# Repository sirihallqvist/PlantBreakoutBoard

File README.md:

# PlantBreakoutBoard

## Prerequisites:
- VSCode
- Arduino Nano 33 BLE connected via usb-usbc to the computer

- ADD MORE AS YOU GO HERE

## Install ArduinoCLI
1. Go to [Arduino CLI Download Page](https://arduino.github.io/arduino-cli/1.3/installation/)
2. Download the correct zip-folder
3. Place the folder where you want to have it
4. Add the path to the .exe file in PATH in environmental variables to be able to use it

## Set up Board

Run the following commands to update and download dependencies.

```powershell
arduino-cli core update-index
arduino-cli core install arduino:mbed_nano  # Installs needed board support for Arduino Nano 33 BLE
```

## Find the FQBN (Fully Qualified Board Name)

Run the following command to find the full name of the board:

```powershell
arduino-cli board listall
```

## Find the Port that the Arduino Use

Run the following command to find which port the Arduino board is using:

```powershell
arduino-cli board list
```

## Compile the Code

To compile the code, run the following command:

```powershell
arduino-cli compile --fqbn arduino:mbed_nano:nano33ble myProjectFolder  # if outside of the folder
arduino-cli compile --fqbn arduino:mbed_nano:nano33ble .  # if inside of the folder
```

## Upload the Code to the Arduino

To upload the code to the unit, run the following command:

```powershell
arduino-cli upload -p <PORT> --fqbn <FQBN> pathToYourProjectFile.ino
```

## Automatic Build and Upload in VSCode

Create the file .vscode/tasks.json in your repository, and add following content in that file:

```json
{
  "version": "2.0.0",
  "tasks": [
    {
      "label": "Build Arduino Sketch",
      "type": "powershell",
      "command": "arduino-cli compile --fqbn arduino:mbed_nano:nano33ble .",
      "group": "build"
    },
    {
      "label": "Upload Arduino Sketch",
      "type": "powershell",
      "command": "arduino-cli upload -p PORT --fqbn FQBN .",
      "group": "build"
    }
  ]
}
```

Now, to build and/or upload, press `Ctrl+Shift+B` and choose the task you want to do.

## Install BLE Library

To install the needed BLE Library, run the following command:

```powershell
arduino-cli lib install ArduinoBLE
```

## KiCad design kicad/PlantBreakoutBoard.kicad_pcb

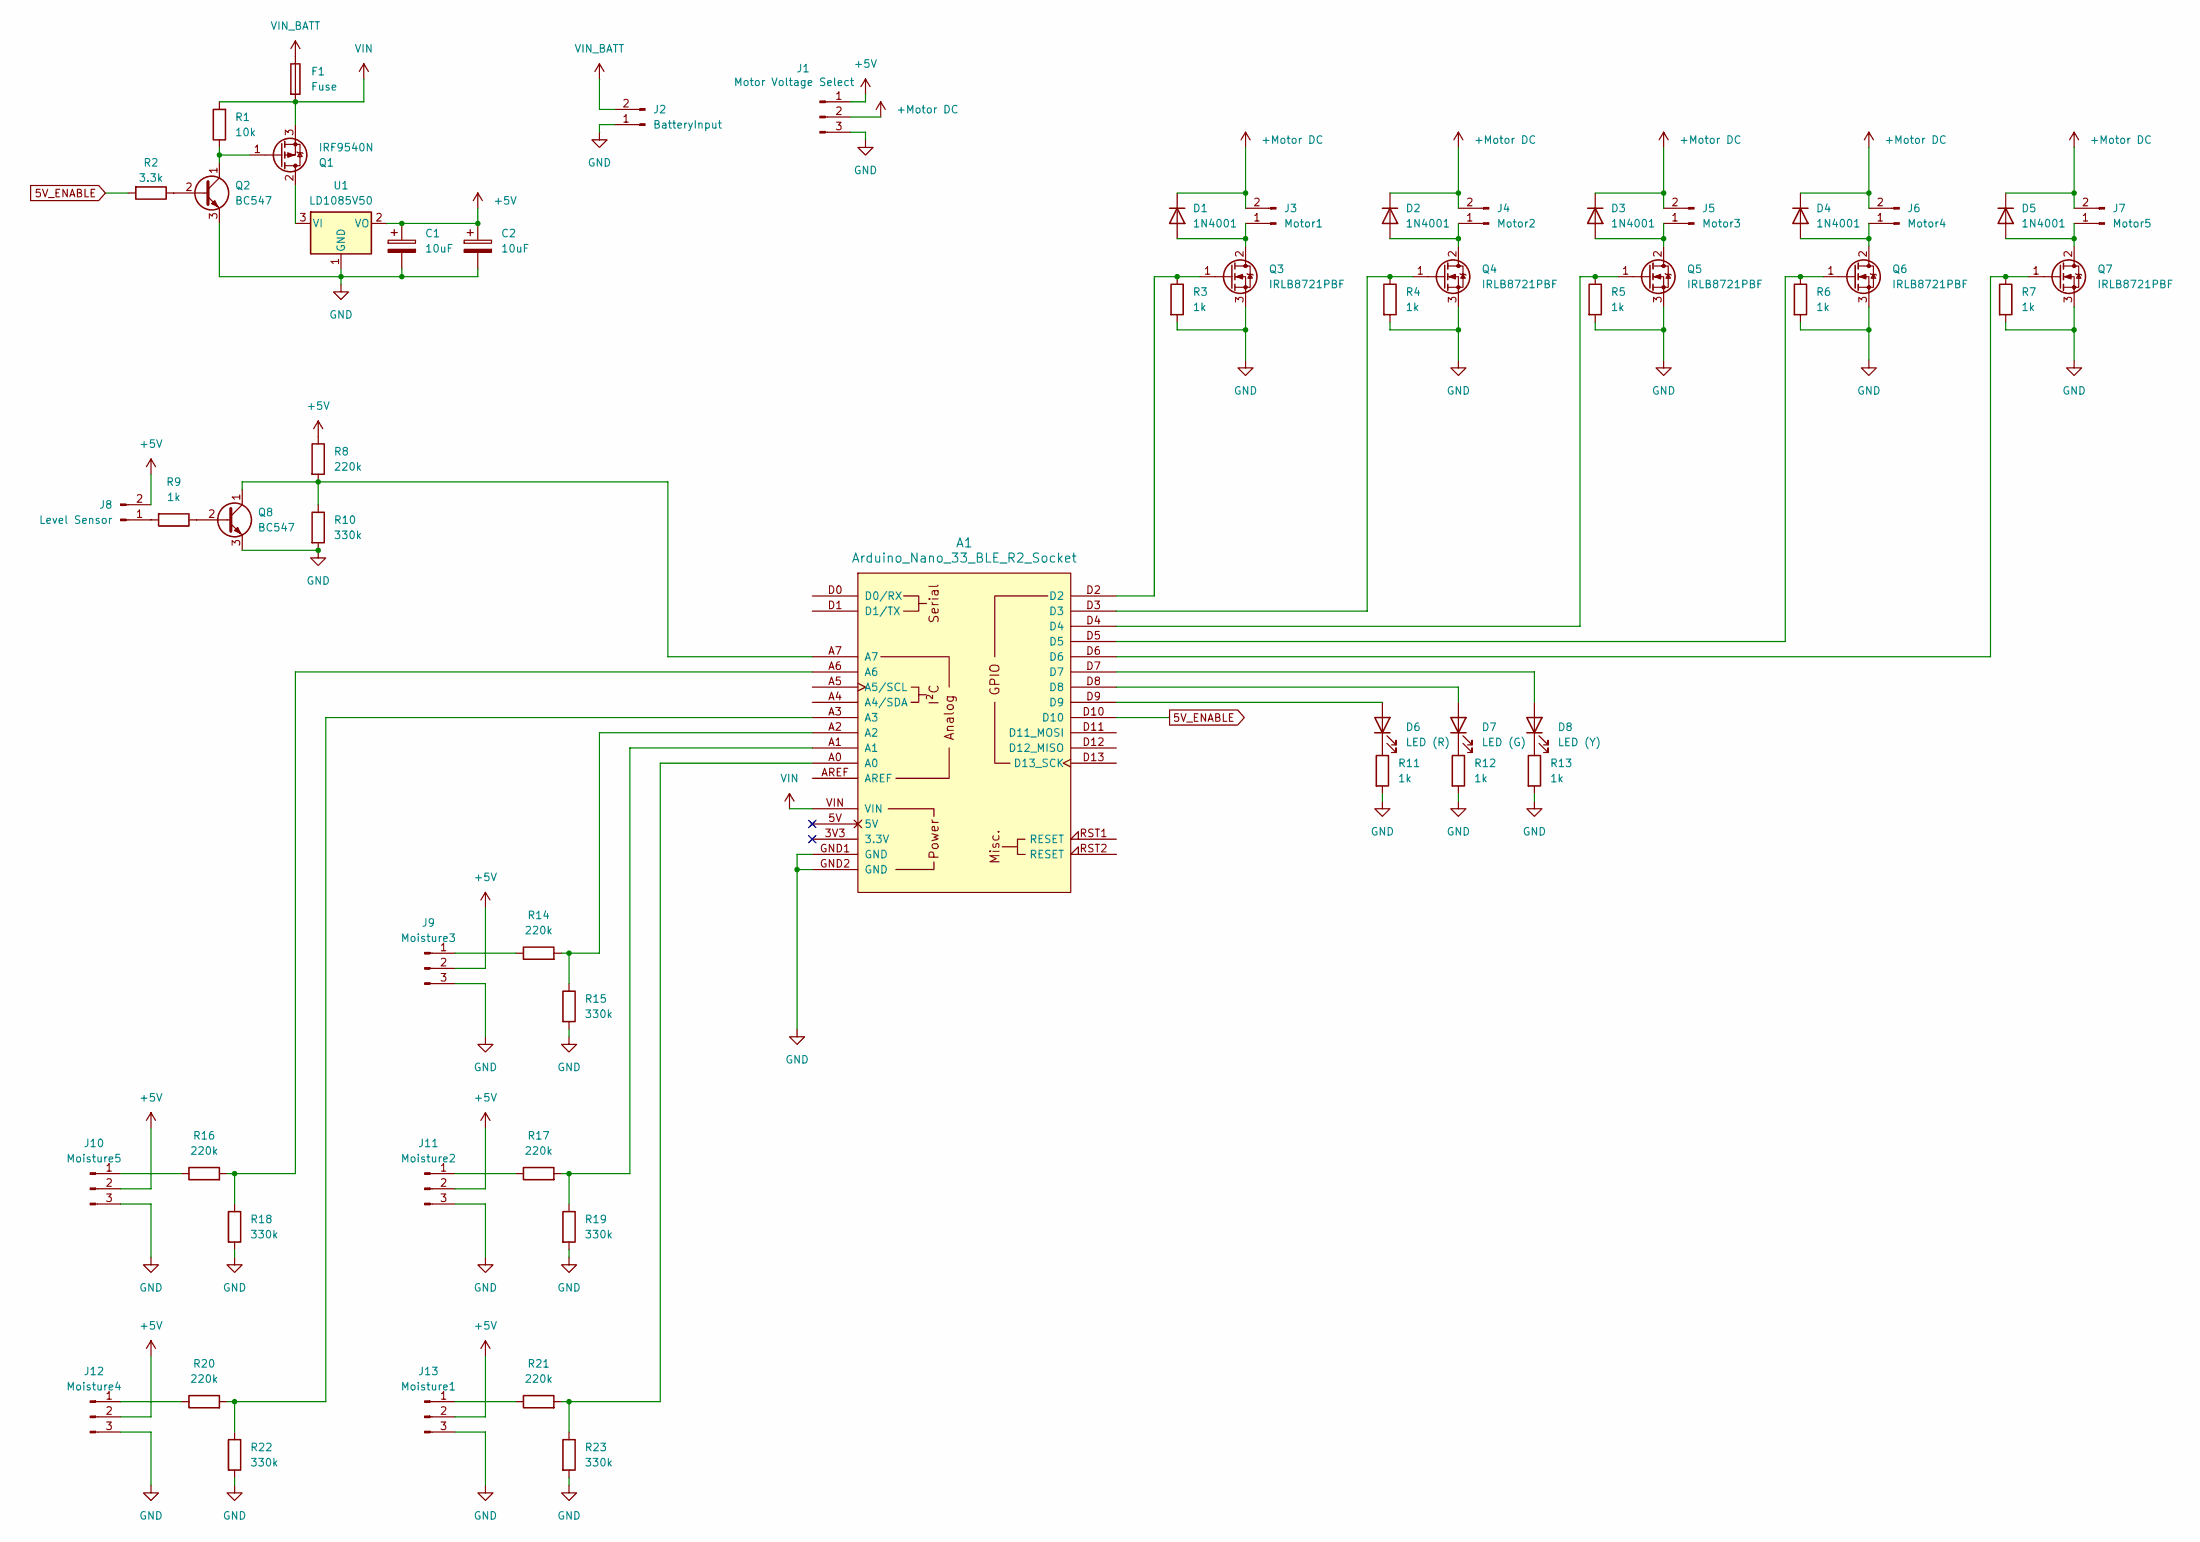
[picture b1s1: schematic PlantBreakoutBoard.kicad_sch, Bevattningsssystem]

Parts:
A1: Arduino_Nano_33_BLE_R2_Socket; Arduino_Nano_Every_Socket
C1, C2: 10uF; CP_Radial_D5.0mm_P2.00mm
D1, D2, D3, D4, D5: 1N4001; D_DO-41_SOD81_P10.16mm_Horizontal
D6: LED (R); LED_D3.0mm
D7: LED (G); LED_D3.0mm
D8: LED (Y); LED_D3.0mm
F1: Fuse; Fuseholder_Cylinder-5x20mm_Stelvio-Kontek_PTF78_Horizontal_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
J1: Motor Voltage Select; PinHeader_1x03_P2.54mm_Vertical
J2: BatteryInput; PinHeader_1x02_P2.54mm_Vertical
J3: Motor1; PinHeader_1x02_P2.54mm_Vertical
J4: Motor2; PinHeader_1x02_P2.54mm_Vertical
J5: Motor3; PinHeader_1x02_P2.54mm_Vertical
J6: Motor4; PinHeader_1x02_P2.54mm_Vertical
J7: Motor5; PinHeader_1x02_P2.54mm_Vertical
J8: Level Sensor; PinHeader_1x02_P2.54mm_Vertical
J9: Moisture3; PinHeader_1x03_P2.54mm_Vertical
J10: Moisture5; PinHeader_1x03_P2.54mm_Vertical
J11: Moisture2; PinHeader_1x03_P2.54mm_Vertical
J12: Moisture4; PinHeader_1x03_P2.54mm_Vertical
J13: Moisture1; PinHeader_1x03_P2.54mm_Vertical
Q1: IRF9540N; TO-220-3_Vertical
Q2, Q8: BC547; TO-92_Inline
Q3, Q4, Q5, Q6, Q7: IRLB8721PBF; TO-220-3_Vertical
R1: 10k; R_Axial_DIN0309_L9.0mm_D3.2mm_P12.70mm_Horizontal
R2: 3.3k; R_Axial_DIN0309_L9.0mm_D3.2mm_P12.70mm_Horizontal
R3, R4, R5, R6, R7, R9, R11, R12, R13: 1k; R_Axial_DIN0309_L9.0mm_D3.2mm_P12.70mm_Horizontal
R8, R14, R16, R17, R20, R21: 220k; R_Axial_DIN0309_L9.0mm_D3.2mm_P12.70mm_Horizontal
R10, R15, R18, R19, R22, R23: 330k; R_Axial_DIN0309_L9.0mm_D3.2mm_P12.70mm_Horizontal
U1: LD1085V50; TO-220-3_Vertical

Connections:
5V_ENABLE: A1.D10, R2.2
+5V: C1.1, C2.1, J1.1, J8.2, J9.2, J10.2, J11.2, J12.2, J13.2, R8.1, U1.2 (VO)
+Motor DC: D1.1 (K), D2.1 (K), D3.1 (K), D4.1 (K), D5.1 (K), J1.2, J3.2, J4.2, J5.2, J6.2, J7.2
GND: A1.GND1 (GND), A1.GND2 (GND), C1.2, C2.2, J1.3, J2.1, J9.3, J10.3, J11.3, J12.3, J13.3, Q2.3 (E), Q3.3 (S), Q4.3 (S), Q5.3 (S), Q6.3 (S), Q7.3 (S), Q8.3 (E), R3.2, R4.2, R5.2, R6.2, R7.2, R10.2, R11.2, R12.2, R13.2, R15.2, R18.2, R19.2, R22.2, R23.2, U1.1 (GND)
unnamed: A1.A0, R21.2, R23.1
unnamed: A1.A1, R17.2, R19.1
unnamed: A1.A2, R14.2, R15.1
unnamed: A1.A3, R20.2, R22.1
unnamed: A1.A6, R16.2, R18.1
unnamed: D1.2 (A), J3.1, Q3.2 (D)
unnamed: D2.2 (A), J4.1, Q4.2 (D)
unnamed: D3.2 (A), J5.1, Q5.2 (D)
unnamed: D4.2 (A), J6.1, Q6.2 (D)
unnamed: D5.2 (A), J7.1, Q7.2 (D)
unnamed: A1.D9, D6.2 (A)
unnamed: D6.1 (K), R11.1
unnamed: A1.D8, D7.2 (A)
unnamed: D7.1 (K), R12.1
unnamed: A1.D7, D8.2 (A)
unnamed: D8.1 (K), R13.1
unnamed: J8.1, R9.2
unnamed: J9.1, R14.1
unnamed: J10.1, R16.1
unnamed: J11.1, R17.1
unnamed: J12.1, R20.1
unnamed: J13.1, R21.1
unnamed: Q1.2 (D), U1.3 (VI)
unnamed: Q1.1 (G), Q2.1 (C), R1.1
unnamed: Q2.2 (B), R2.1
unnamed: A1.D2, Q3.1 (G), R3.1
unnamed: A1.D3, Q4.1 (G), R4.1
unnamed: A1.D4, Q5.1 (G), R5.1
unnamed: A1.D5, Q6.1 (G), R6.1
unnamed: A1.D6, Q7.1 (G), R7.1
unnamed: Q8.2 (B), R9.1
unnamed: A1.A7, Q8.1 (C), R8.2, R10.1
VIN: A1.VIN, F1.2, Q1.3 (S), R1.2
VIN_BATT: F1.1, J2.2

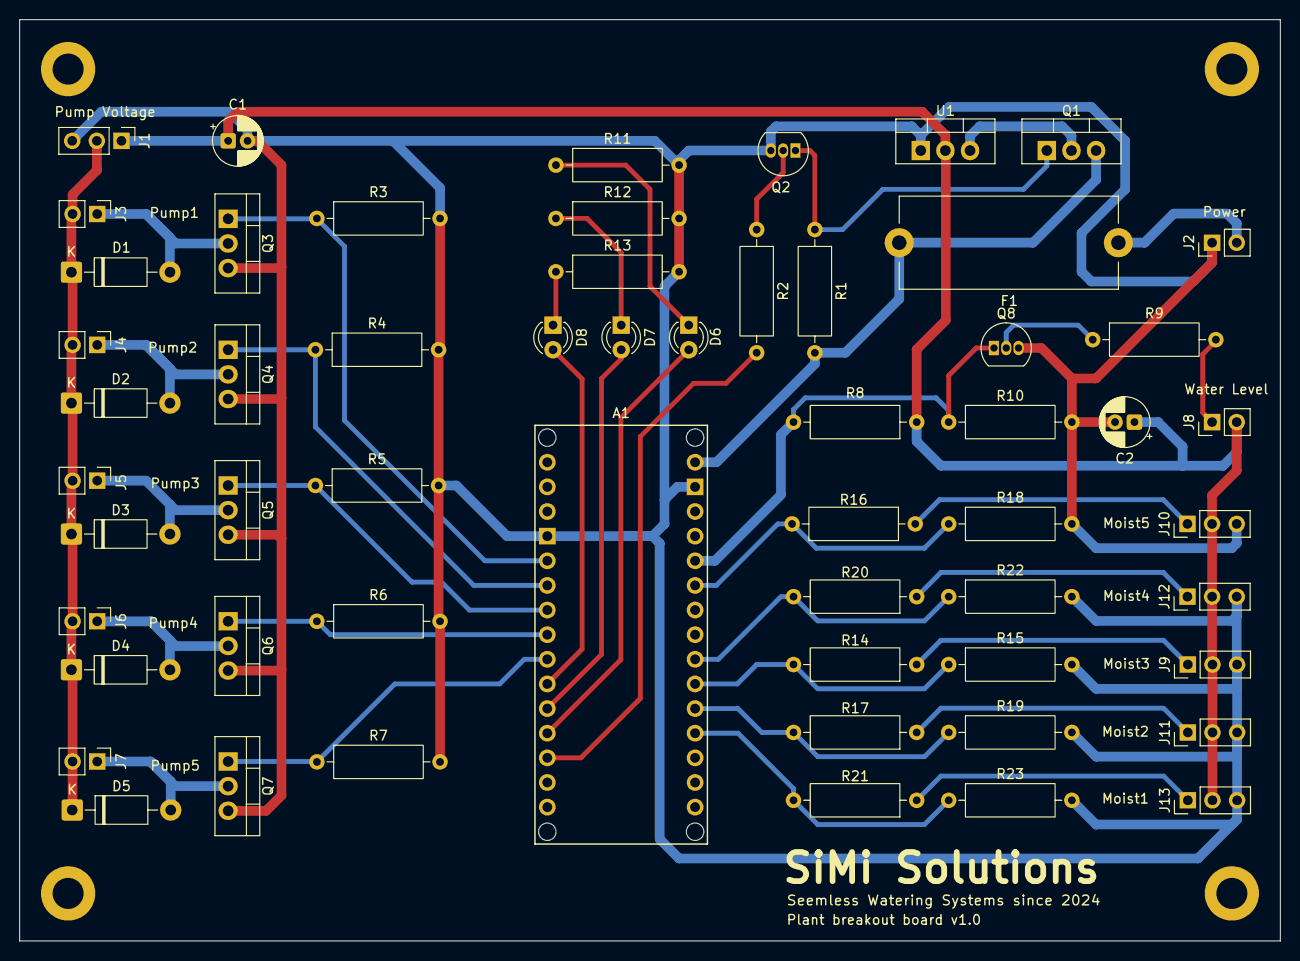
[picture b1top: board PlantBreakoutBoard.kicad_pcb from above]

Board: 2 copper layers, 130.0 x 95.0 mm, 61 parts (0 on the bottom side), 38 nets.

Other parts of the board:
hole1, hole2, hole3, hole4: MountingHole_3.2mm_M3_DIN965_Pad

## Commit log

2025-09-03 First commit, some documentation
2025-09-03 Adding working arduino-cli solution, with simple blink example test
2025-09-03 Fixes
2025-09-14 Some handlers and PlantBreakoutBoard.ino file
2025-09-28 added kicad files
